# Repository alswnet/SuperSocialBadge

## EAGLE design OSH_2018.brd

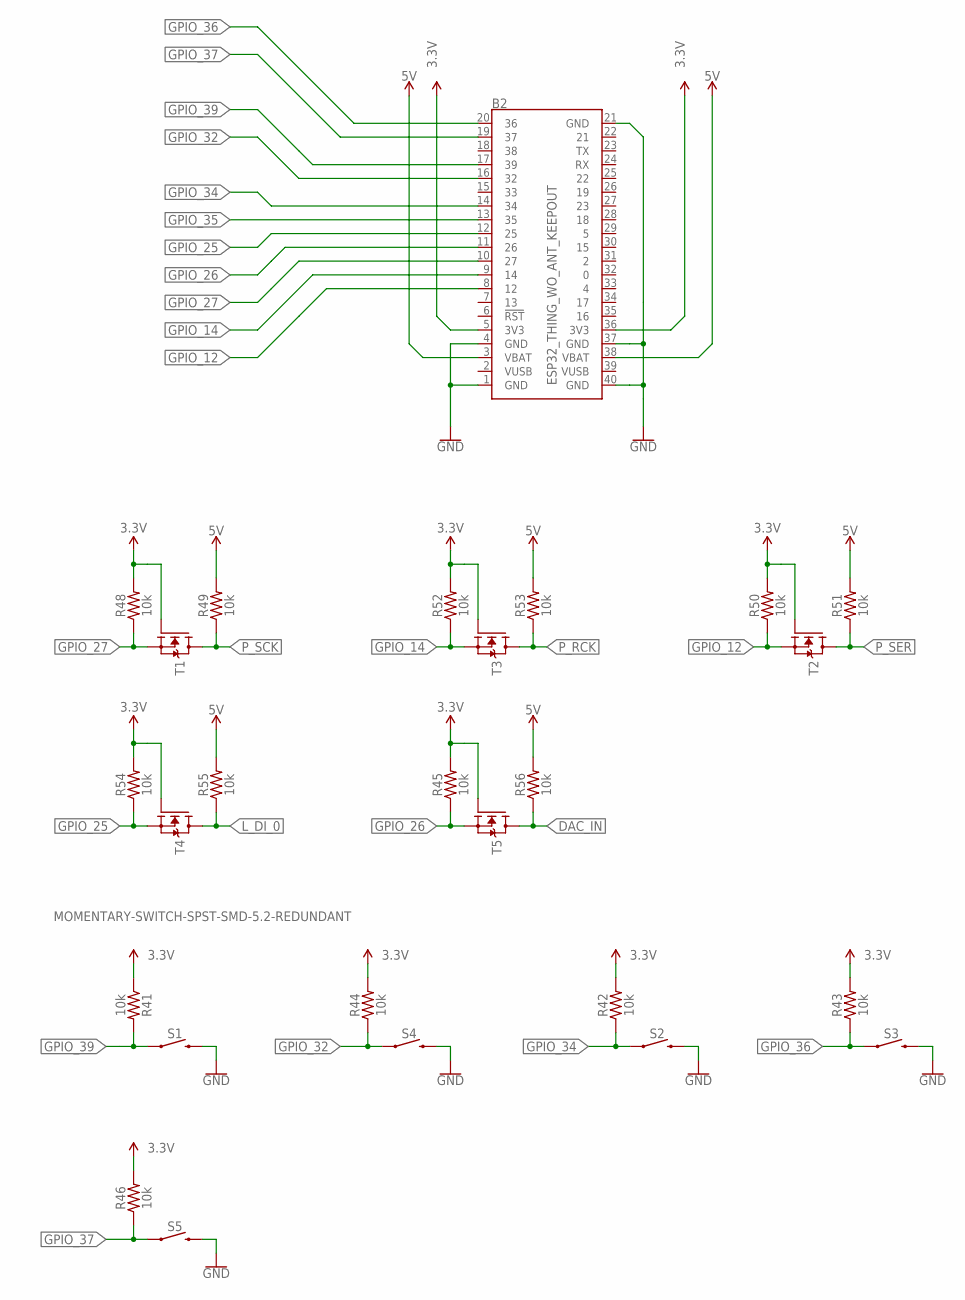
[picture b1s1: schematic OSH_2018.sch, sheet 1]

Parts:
B2: ESP32_THING_WO_ANT_KEEPOUT; ESP32_THING_NO_ANT
R41, R42, R43, R44, R45, R46, R48, R49, R50, R51, R52, R53, R54, R55, R56: 10k; 0603
S1, S2, S3, S4, S5: MOMENTARY-SWITCH-SPST-SMD-5.2-REDUNDANT; TACTILE_SWITCH_SMD_5.2MM
T1, T2, T3, T4, T5: MOSFET-N-SOT23; SOT23

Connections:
3.3V: B2.5 (3V3), B2.36 (3V3), R41.1, R42.2, R43.2, R44.2, R45.2, R46.2, R48.2, R50.2, R52.2, R54.2, T1.1 (G), T2.1 (G), T3.1 (G), T4.1 (G), T5.1 (G)
5V: B2.3 (VBAT), B2.38 (VBAT), R49.2, R51.2, R53.2, R55.2, R56.2; also elsewhere on the board
DAC_IN: R56.1, T5.3 (D); also elsewhere on the board
GND: B2.1 (GND), B2.4 (GND), B2.21 (GND), B2.37 (GND), B2.40 (GND), S1.3 (2), S1.4 (2), S2.3 (2), S2.4 (2), S3.3 (2), S3.4 (2), S4.3 (2), S4.4 (2), S5.3 (2), S5.4 (2); also elsewhere on the board
GPIO_12: B2.8 (12), R50.1, T2.2 (S)
GPIO_14: B2.9 (14), R52.1, T3.2 (S)
GPIO_25: B2.12 (25), R54.1, T4.2 (S)
GPIO_26: B2.11 (26), R45.1, T5.2 (S)
GPIO_27: B2.10 (27), R48.1, T1.2 (S)
GPIO_32: B2.16 (32), R44.1, S4.1, S4.2 (1)
GPIO_34: B2.14 (34), R42.1, S2.1, S2.2 (1)
GPIO_35: B2.13 (35); also elsewhere on the board
GPIO_36: B2.20 (36), R43.1, S3.1, S3.2 (1)
GPIO_37: B2.19 (37), R46.1, S5.1, S5.2 (1)
GPIO_39: B2.17 (39), R41.2, S1.1, S1.2 (1)
L_DI_0: R55.1, T4.3 (D); also elsewhere on the board
P_RCK: R53.1, T3.3 (D); also elsewhere on the board
P_SCK: R49.1, T1.3 (D); also elsewhere on the board
P_SER: R51.1, T2.3 (D); also elsewhere on the board

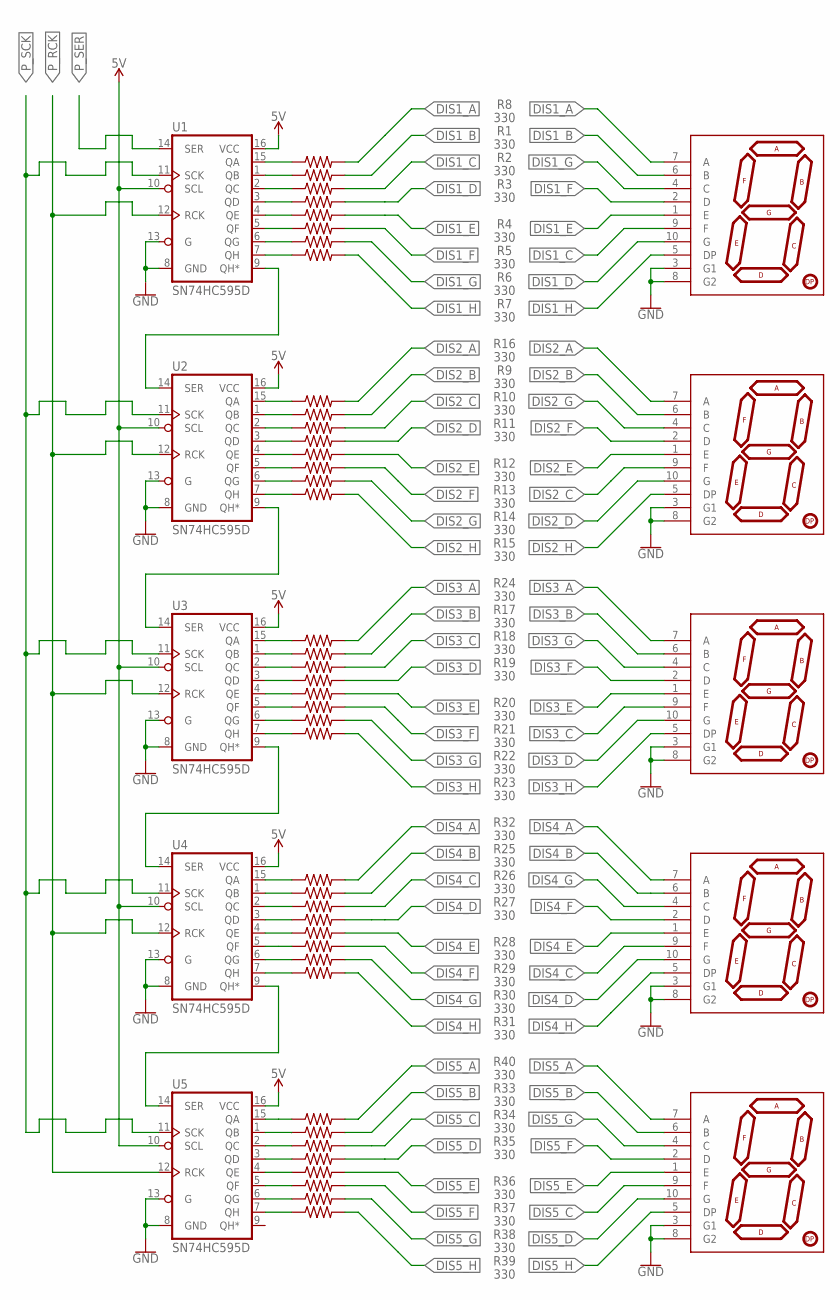
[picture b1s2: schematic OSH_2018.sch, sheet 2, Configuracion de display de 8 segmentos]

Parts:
DISPLAY_1, DISPLAY_2, DISPLAY_3, DISPLAY_4, DISPLAY_5: YSD-160AB3C-8; 7-SEGMENT-1"PTH
R1, R2, R3, R4, R5, R6, R7, R8, R9, R10, R11, R12, R13, R14, R15, R16, R17, R18, R19, R20, R21, R22, R23, R24, R25, R26, R27, R28, R29, R30, R31, R32, R33, R34, R35, R36, R37, R38, R39, R40: 330; 0603
U1, U2, U3, U4, U5: SN74HC595D; SO16

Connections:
5V: U1.10 (SCL), U1.16 (VCC), U2.10 (SCL), U2.16 (VCC), U3.10 (SCL), U3.16 (VCC), U4.10 (SCL), U4.16 (VCC), U5.10 (SCL), U5.16 (VCC); also elsewhere on the board
DIS1_A: DISPLAY_1.7 (A), R8.2
DIS1_B: DISPLAY_1.6 (B), R1.2
DIS1_C: DISPLAY_1.9 (F), R2.2
DIS1_D: DISPLAY_1.10 (G), R3.2
DIS1_E: DISPLAY_1.1 (E), R4.2
DIS1_F: DISPLAY_1.2 (D), R5.2
DIS1_G: DISPLAY_1.4 (C), R6.2
DIS1_H: DISPLAY_1.5 (DP), R7.2
DIS2_A: DISPLAY_2.7 (A), R9.2
DIS2_B: DISPLAY_2.6 (B), R10.2
DIS2_C: DISPLAY_2.9 (F), R11.2
DIS2_D: DISPLAY_2.10 (G), R12.2
DIS2_E: DISPLAY_2.1 (E), R13.2
DIS2_F: DISPLAY_2.2 (D), R14.2
DIS2_G: DISPLAY_2.4 (C), R15.2
DIS2_H: DISPLAY_2.5 (DP), R16.2
DIS3_A: DISPLAY_3.7 (A), R17.2
DIS3_B: DISPLAY_3.6 (B), R18.2
DIS3_C: DISPLAY_3.9 (F), R19.2
DIS3_D: DISPLAY_3.10 (G), R20.2
DIS3_E: DISPLAY_3.1 (E), R21.2
DIS3_F: DISPLAY_3.2 (D), R22.2
DIS3_G: DISPLAY_3.4 (C), R23.2
DIS3_H: DISPLAY_3.5 (DP), R24.2
DIS4_A: DISPLAY_4.7 (A), R25.2
DIS4_B: DISPLAY_4.6 (B), R26.2
DIS4_C: DISPLAY_4.9 (F), R27.2
DIS4_D: DISPLAY_4.10 (G), R28.2
DIS4_E: DISPLAY_4.1 (E), R29.2
DIS4_F: DISPLAY_4.2 (D), R30.2
DIS4_G: DISPLAY_4.4 (C), R31.2
DIS4_H: DISPLAY_4.5 (DP), R32.2
DIS5_A: DISPLAY_5.7 (A), R33.2
DIS5_B: DISPLAY_5.6 (B), R34.2
DIS5_C: DISPLAY_5.9 (F), R35.2
DIS5_D: DISPLAY_5.10 (G), R36.2
DIS5_E: DISPLAY_5.1 (E), R37.2
DIS5_F: DISPLAY_5.2 (D), R38.2
DIS5_G: DISPLAY_5.4 (C), R39.2
DIS5_H: DISPLAY_5.5 (DP), R40.2
GND: DISPLAY_1.3 (G1), DISPLAY_1.8 (G2), DISPLAY_2.3 (G1), DISPLAY_2.8 (G2), DISPLAY_3.3 (G1), DISPLAY_3.8 (G2), DISPLAY_4.3 (G1), DISPLAY_4.8 (G2), DISPLAY_5.3 (G1), DISPLAY_5.8 (G2), U1.8 (GND), U1.13 (G), U2.8 (GND), U2.13 (G), U3.8 (GND), U3.13 (G), U4.8 (GND), U4.13 (G), U5.8 (GND), U5.13 (G); also elsewhere on the board
unnamed: R8.1, U1.15 (QA)
unnamed: R1.1, U1.1 (QB)
unnamed: R2.1, U1.2 (QC)
unnamed: R3.1, U1.3 (QD)
unnamed: R4.1, U1.4 (QE)
unnamed: R5.1, U1.5 (QF)
unnamed: R6.1, U1.6 (QG)
unnamed: R7.1, U1.7 (QH)
unnamed: R9.1, U2.15 (QA)
unnamed: R10.1, U2.1 (QB)
unnamed: R11.1, U2.2 (QC)
unnamed: R12.1, U2.3 (QD)
unnamed: R13.1, U2.4 (QE)
unnamed: R14.1, U2.5 (QF)
unnamed: R15.1, U2.6 (QG)
unnamed: R16.1, U2.7 (QH)
unnamed: R17.1, U3.15 (QA)
unnamed: R18.1, U3.1 (QB)
unnamed: R19.1, U3.2 (QC)
unnamed: R20.1, U3.3 (QD)
unnamed: R21.1, U3.4 (QE)
unnamed: R22.1, U3.5 (QF)
unnamed: R23.1, U3.6 (QG)
unnamed: R24.1, U3.7 (QH)
unnamed: R25.1, U4.15 (QA)
unnamed: R26.1, U4.1 (QB)
unnamed: R27.1, U4.2 (QC)
unnamed: R28.1, U4.3 (QD)
unnamed: R29.1, U4.4 (QE)
unnamed: R30.1, U4.5 (QF)
unnamed: R31.1, U4.6 (QG)
unnamed: R32.1, U4.7 (QH)
unnamed: R33.1, U5.15 (QA)
unnamed: R34.1, U5.1 (QB)
unnamed: R35.1, U5.2 (QC)
unnamed: R36.1, U5.3 (QD)
unnamed: R37.1, U5.4 (QE)
unnamed: R38.1, U5.5 (QF)
unnamed: R39.1, U5.6 (QG)
unnamed: R40.1, U5.7 (QH)
unnamed: U1.9 (QH*), U2.14 (SER)
unnamed: U2.9 (QH*), U3.14 (SER)
unnamed: U3.9 (QH*), U4.14 (SER)
unnamed: U4.9 (QH*), U5.14 (SER)
P_RCK: U1.12 (RCK), U2.12 (RCK), U3.12 (RCK), U4.12 (RCK), U5.12 (RCK); also elsewhere on the board
P_SCK: U1.11 (SCK), U2.11 (SCK), U3.11 (SCK), U4.11 (SCK), U5.11 (SCK); also elsewhere on the board
P_SER: U1.14 (SER); also elsewhere on the board

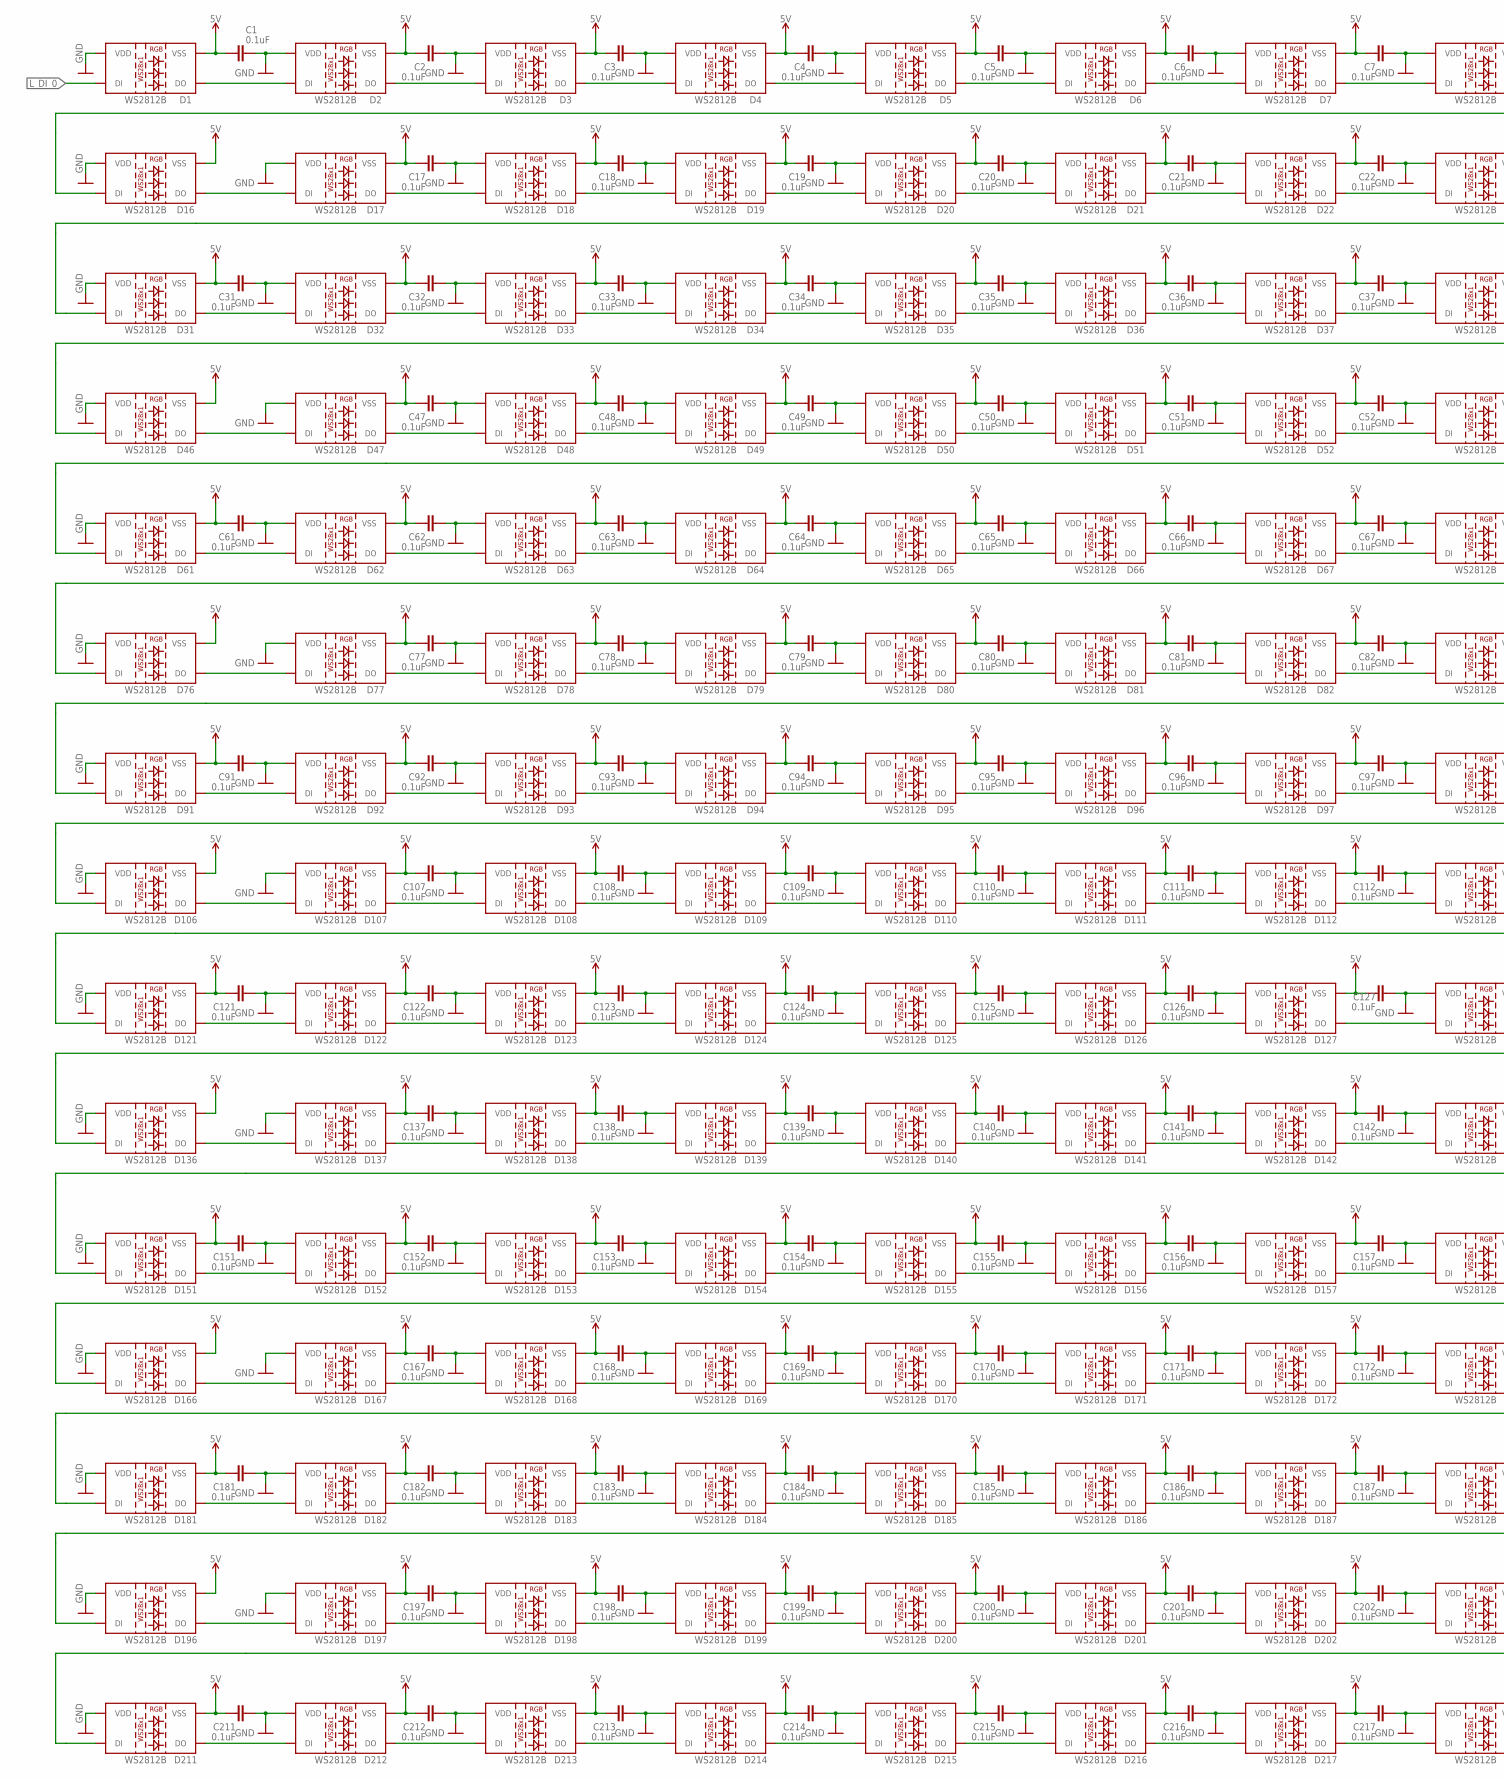
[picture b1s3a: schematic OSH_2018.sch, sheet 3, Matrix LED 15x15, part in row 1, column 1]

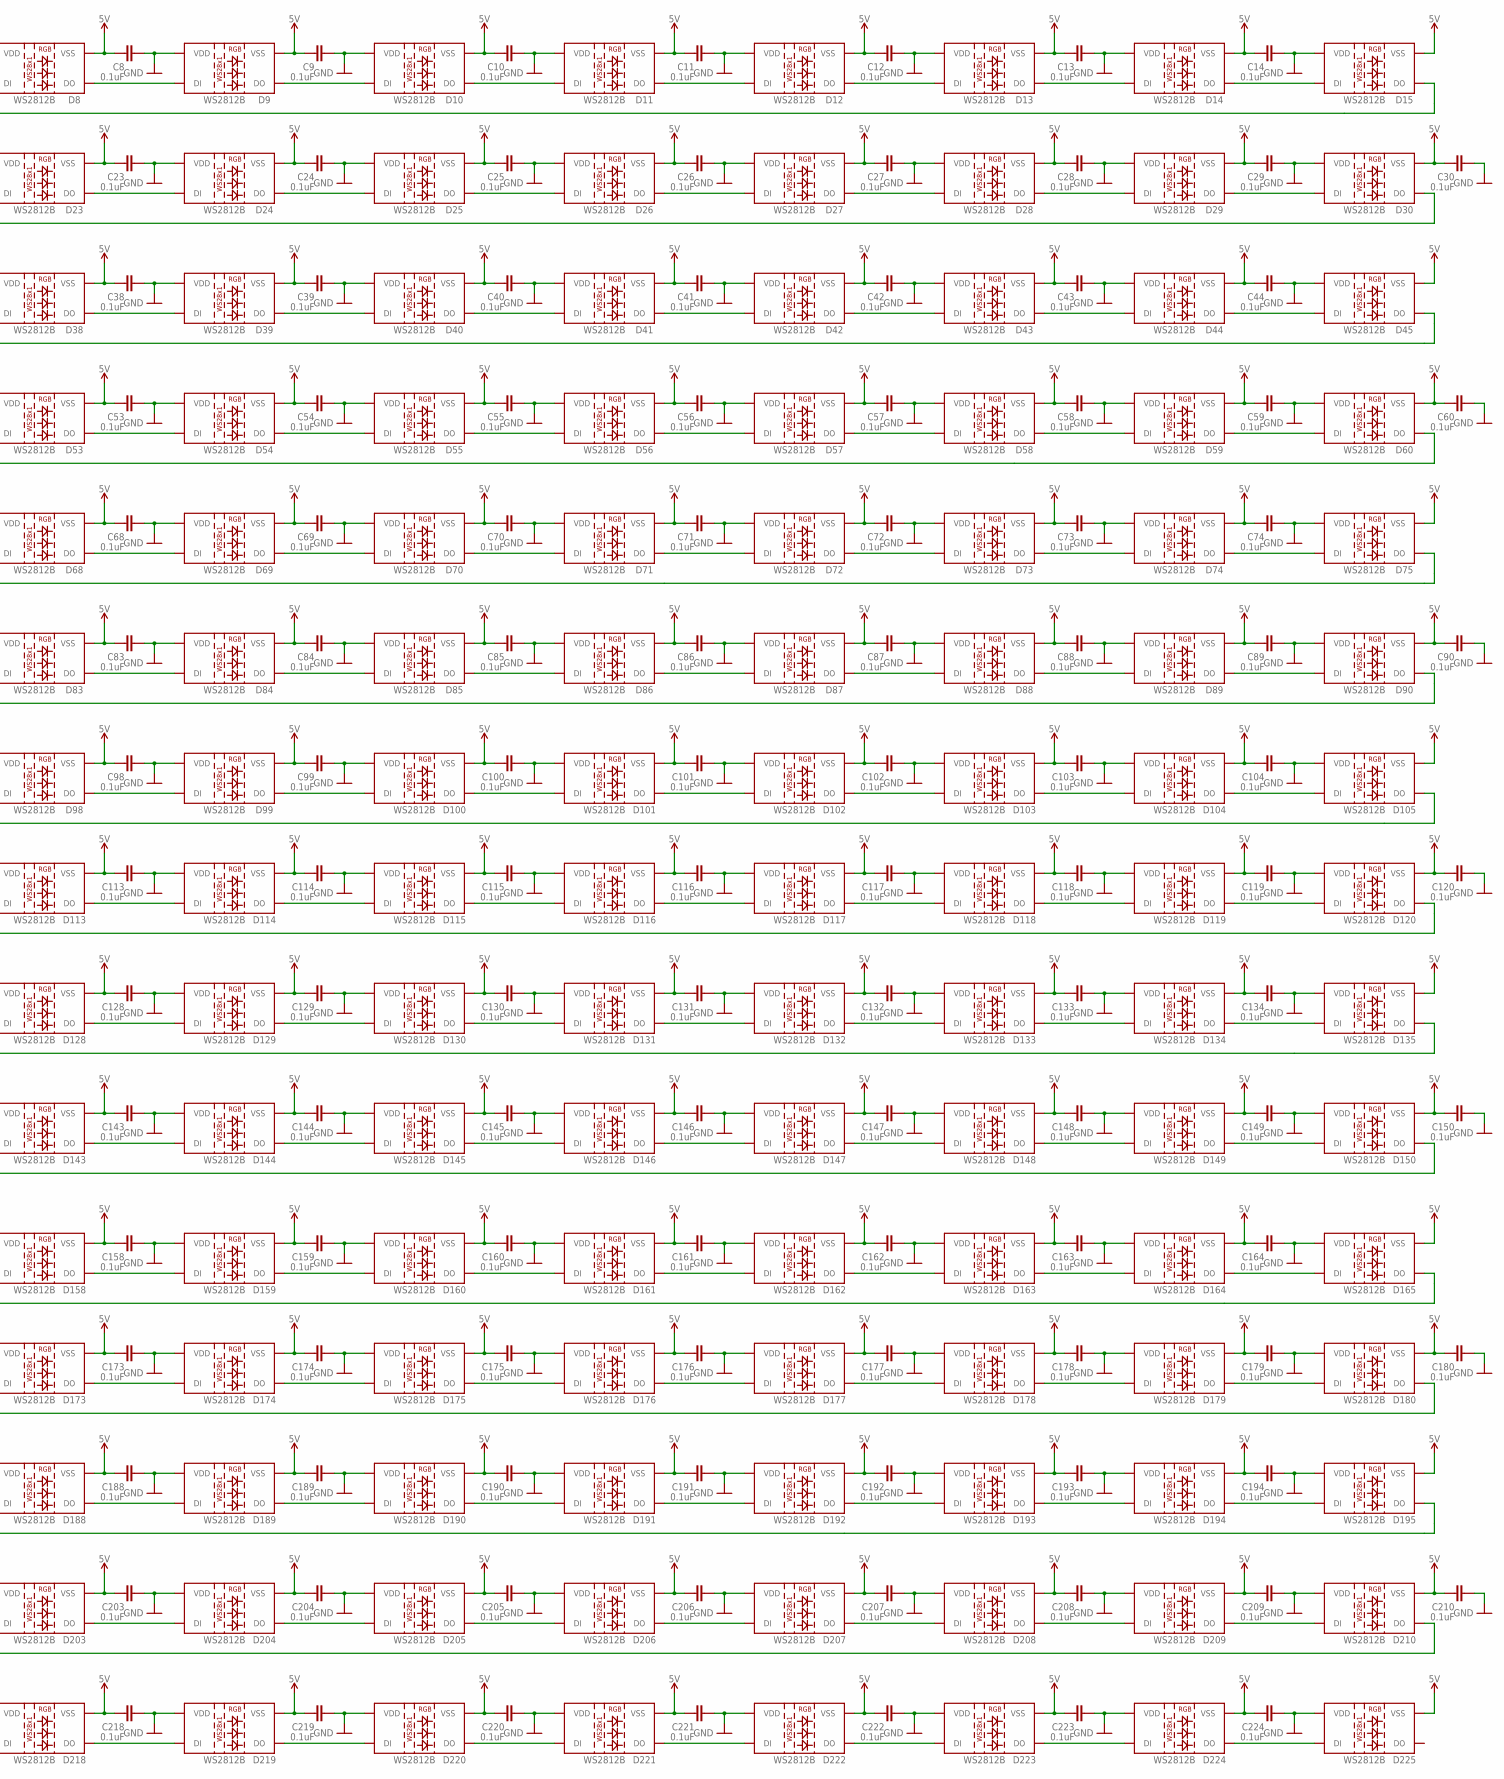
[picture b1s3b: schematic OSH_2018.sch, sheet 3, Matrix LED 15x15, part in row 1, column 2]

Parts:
C1, C2, C3, C4, C5, C6, C7, C8, C9, C10, C11, C12, C13, C14, C17, C18, C19, C20, C21, C22, C23, C24, C25, C26, C27, C28, C29, C30, C31, C32, C33, C34, C35, C36, C37, C38, C39, C40, C41, C42, C43, C44, C47, C48, C49, C50, C51, C52, C53, C54, C55, C56, C57, C58, C59, C60, C61, C62, C63, C64, C65, C66, C67, C68, C69, C70, C71, C72, C73, C74, C77, C78, C79, C80, C81, C82, C83, C84, C85, C86, C87, C88, C89, C90, C91, C92, C93, C94, C95, C96, C97, C98, C99, C100, C101, C102, C103, C104, C107, C108, C109, C110, C111, C112, C113, C114, C115, C116, C117, C118, C119, C120, C121, C122, C123, C124, C125, C126, C127, C128, C129, C130, C131, C132, C133, C134, C137, C138, C139, C140, C141, C142, C143, C144, C145, C146, C147, C148, C149, C150, C151, C152, C153, C154, C155, C156, C157, C158, C159, C160, C161, C162, C163, C164, C167, C168, C169, C170, C171, C172, C173, C174, C175, C176, C177, C178, C179, C180, C181, C182, C183, C184, C185, C186, C187, C188, C189, C190, C191, C192, C193, C194, C197, C198, C199, C200, C201, C202, C203, C204, C205, C206, C207, C208, C209, C210, C211, C212, C213, C214, C215, C216, C217, C218, C219, C220, C221, C222, C223, C224: 0.1uF; 0603
D1, D2, D3, D4, D5, D6, D7, D8, D9, D10, D11, D12, D13, D14, D15, D16, D17, D18, D19, D20, D21, D22, D23, D24, D25, D26, D27, D28, D29, D30, D31, D32, D33, D34, D35, D36, D37, D38, D39, D40, D41, D42, D43, D44, D45, D46, D47, D48, D49, D50, D51, D52, D53, D54, D55, D56, D57, D58, D59, D60, D61, D62, D63, D64, D65, D66, D67, D68, D69, D70, D71, D72, D73, D74, D75, D76, D77, D78, D79, D80, D81, D82, D83, D84, D85, D86, D87, D88, D89, D90, D91, D92, D93, D94, D95, D96, D97, D98, D99, D100, D101, D102, D103, D104, D105, D106, D107, D108, D109, D110, D111, D112, D113, D114, D115, D116, D117, D118, D119, D120, D121, D122, D123, D124, D125, D126, D127, D128, D129, D130, D131, D132, D133, D134, D135, D136, D137, D138, D139, D140, D141, D142, D143, D144, D145, D146, D147, D148, D149, D150, D151, D152, D153, D154, D155, D156, D157, D158, D159, D160, D161, D162, D163, D164, D165, D166, D167, D168, D169, D170, D171, D172, D173, D174, D175, D176, D177, D178, D179, D180, D181, D182, D183, D184, D185, D186, D187, D188, D189, D190, D191, D192, D193, D194, D195, D196, D197, D198, D199, D200, D201, D202, D203, D204, D205, D206, D207, D208, D209, D210, D211, D212, D213, D214, D215, D216, D217, D218, D219, D220, D221, D222, D223, D224, D225: WS2812B

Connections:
5V: C1.1, C2.1, C3.1, C4.1, C5.1, C6.1, C7.1, C8.1, C9.1, C10.1, C11.1, C12.1, C13.1, C14.1, C17.1, C18.1, C19.1, C20.1, C21.1, C22.1, C23.1, C24.1, C25.1, C26.1, C27.1, C28.1, C29.1, C30.1, C31.1, C32.1, C33.1, C34.1, C35.1, C36.1, C37.1, C38.1, C39.1, C40.1, C41.1, C42.1, C43.1, C44.1, C47.1, C48.1, C49.1, C50.1, C51.1, C52.1, C53.1, C54.1, C55.1, C56.1, C57.1, C58.1, C59.1, C60.1, C61.1, C62.1, C63.1, C64.1, C65.1, C66.1, C67.1, C68.1, C69.1, C70.1, C71.1, C72.1, C73.1, C74.1, C77.1, C78.1, C79.1, C80.1, C81.1, C82.1, C83.1, C84.1, C85.1, C86.1, C87.1, C88.1, C89.1, C90.1, C91.1, C92.1, C93.1, C94.1, C95.1, C96.1, C97.1, C98.1, C99.1, C100.1, C101.1, C102.1, C103.1, C104.1, C107.1, C108.1, C109.1, C110.1, C111.1, C112.1, C113.1, C114.1, C115.1, C116.1, C117.1, C118.1, C119.1, C120.1, C121.1, C122.1, C123.1, C124.1, C125.1, C126.1, C127.1, C128.1, C129.1, C130.1, C131.1, C132.1, C133.1, C134.1, C137.1, C138.1, C139.1, C140.1, C141.1, C142.1, C143.1, C144.1, C145.1, C146.1, C147.1, C148.1, C149.1, C150.1, C151.1, C152.1, C153.1, C154.1, C155.1, C156.1, C157.1, C158.1, C159.1, C160.1, C161.1, C162.1, C163.1, C164.1, C167.1, C168.1, C169.1, C170.1, C171.1, C172.1, C173.1, C174.1, C175.1, C176.1, C177.1, C178.1, C179.1, C180.1, C181.1, C182.1, C183.1, C184.1, C185.1, C186.1, C187.1, C188.1, C189.1, C190.1, C191.1, C192.1, C193.1, C194.1, C197.1, C198.1, C199.1, C200.1, C201.1, C202.1, C203.1, C204.1, C205.1, C206.1, C207.1, C208.1, C209.1, C210.1, C211.1, C212.1, C213.1, C214.1, C215.1, C216.1, C217.1, C218.1, C219.1, C220.1, C221.1, C222.1, C223.1, C224.1, D1.3 (VSS), D2.3 (VSS), D3.3 (VSS), D4.3 (VSS), D5.3 (VSS), D6.3 (VSS), D7.3 (VSS), D8.3 (VSS), D9.3 (VSS), D10.3 (VSS), D11.3 (VSS), D12.3 (VSS), D13.3 (VSS), D14.3 (VSS), D15.3 (VSS), D16.3 (VSS), D17.3 (VSS), D18.3 (VSS), D19.3 (VSS), D20.3 (VSS), D21.3 (VSS), D22.3 (VSS), D23.3 (VSS), D24.3 (VSS), D25.3 (VSS), D26.3 (VSS), D27.3 (VSS), D28.3 (VSS), D29.3 (VSS), D30.3 (VSS), D31.3 (VSS), D32.3 (VSS), D33.3 (VSS), D34.3 (VSS), D35.3 (VSS), D36.3 (VSS), D37.3 (VSS), D38.3 (VSS), D39.3 (VSS), D40.3 (VSS), D41.3 (VSS), D42.3 (VSS), D43.3 (VSS), D44.3 (VSS), D45.3 (VSS), D46.3 (VSS), D47.3 (VSS), D48.3 (VSS), D49.3 (VSS), D50.3 (VSS), D51.3 (VSS), D52.3 (VSS), D53.3 (VSS), D54.3 (VSS), D55.3 (VSS), D56.3 (VSS), D57.3 (VSS), D58.3 (VSS), D59.3 (VSS), D60.3 (VSS), D61.3 (VSS), D62.3 (VSS), D63.3 (VSS), D64.3 (VSS), D65.3 (VSS), D66.3 (VSS), D67.3 (VSS), D68.3 (VSS), D69.3 (VSS), D70.3 (VSS), D71.3 (VSS), D72.3 (VSS), D73.3 (VSS), D74.3 (VSS), D75.3 (VSS), D76.3 (VSS), D77.3 (VSS), D78.3 (VSS), D79.3 (VSS), D80.3 (VSS), D81.3 (VSS), D82.3 (VSS), D83.3 (VSS), D84.3 (VSS), D85.3 (VSS), D86.3 (VSS), D87.3 (VSS), D88.3 (VSS), D89.3 (VSS), D90.3 (VSS), D91.3 (VSS), D92.3 (VSS), D93.3 (VSS), D94.3 (VSS), D95.3 (VSS), D96.3 (VSS), D97.3 (VSS), D98.3 (VSS), D99.3 (VSS), D100.3 (VSS), D101.3 (VSS), D102.3 (VSS), D103.3 (VSS), D104.3 (VSS), D105.3 (VSS), D106.3 (VSS), D107.3 (VSS), D108.3 (VSS), D109.3 (VSS), D110.3 (VSS), D111.3 (VSS), D112.3 (VSS), D113.3 (VSS), D114.3 (VSS), D115.3 (VSS), D116.3 (VSS), D117.3 (VSS), D118.3 (VSS), D119.3 (VSS), D120.3 (VSS), D121.3 (VSS), D122.3 (VSS), D123.3 (VSS), D124.3 (VSS), D125.3 (VSS), D126.3 (VSS), D127.3 (VSS), D128.3 (VSS), D129.3 (VSS), D130.3 (VSS), D131.3 (VSS), D132.3 (VSS), D133.3 (VSS), D134.3 (VSS), D135.3 (VSS), D136.3 (VSS), D137.3 (VSS), D138.3 (VSS), D139.3 (VSS), D140.3 (VSS), D141.3 (VSS), D142.3 (VSS), D143.3 (VSS), D144.3 (VSS), D145.3 (VSS), D146.3 (VSS), D147.3 (VSS), D148.3 (VSS), D149.3 (VSS), D150.3 (VSS), D151.3 (VSS), D152.3 (VSS)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; also elsewhere on the board
GND: C1.2, C2.2, C3.2, C4.2, C5.2, C6.2, C7.2, C8.2, C9.2, C10.2, C11.2, C12.2, C13.2, C14.2, C17.2, C18.2, C19.2, C20.2, C21.2, C22.2, C23.2, C24.2, C25.2, C26.2, C27.2, C28.2, C29.2, C30.2, C31.2, C32.2, C33.2, C34.2, C35.2, C36.2, C37.2, C38.2, C39.2, C40.2, C41.2, C42.2, C43.2, C44.2, C47.2, C48.2, C49.2, C50.2, C51.2, C52.2, C53.2, C54.2, C55.2, C56.2, C57.2, C58.2, C59.2, C60.2, C61.2, C62.2, C63.2, C64.2, C65.2, C66.2, C67.2, C68.2, C69.2, C70.2, C71.2, C72.2, C73.2, C74.2, C77.2, C78.2, C79.2, C80.2, C81.2, C82.2, C83.2, C84.2, C85.2, C86.2, C87.2, C88.2, C89.2, C90.2, C91.2, C92.2, C93.2, C94.2, C95.2, C96.2, C97.2, C98.2, C99.2, C100.2, C101.2, C102.2, C103.2, C104.2, C107.2, C108.2, C109.2, C110.2, C111.2, C112.2, C113.2, C114.2, C115.2, C116.2, C117.2, C118.2, C119.2, C120.2, C121.2, C122.2, C123.2, C124.2, C125.2, C126.2, C127.2, C128.2, C129.2, C130.2, C131.2, C132.2, C133.2, C134.2, C137.2, C138.2, C139.2, C140.2, C141.2, C142.2, C143.2, C144.2, C145.2, C146.2, C147.2, C148.2, C149.2, C150.2, C151.2, C152.2, C153.2, C154.2, C155.2, C156.2, C157.2, C158.2, C159.2, C160.2, C161.2, C162.2, C163.2, C164.2, C167.2, C168.2, C169.2, C170.2, C171.2, C172.2, C173.2, C174.2, C175.2, C176.2, C177.2, C178.2, C179.2, C180.2, C181.2, C182.2, C183.2, C184.2, C185.2, C186.2, C187.2, C188.2, C189.2, C190.2, C191.2, C192.2, C193.2, C194.2, C197.2, C198.2, C199.2, C200.2, C201.2, C202.2, C203.2, C204.2, C205.2, C206.2, C207.2, C208.2, C209.2, C210.2, C211.2, C212.2, C213.2, C214.2, C215.2, C216.2, C217.2, C218.2, C219.2, C220.2, C221.2, C222.2, C223.2, C224.2, D1.1 (VDD), D2.1 (VDD), D3.1 (VDD), D4.1 (VDD), D5.1 (VDD), D6.1 (VDD), D7.1 (VDD), D8.1 (VDD), D9.1 (VDD), D10.1 (VDD), D11.1 (VDD), D12.1 (VDD), D13.1 (VDD), D14.1 (VDD), D15.1 (VDD), D16.1 (VDD), D17.1 (VDD), D18.1 (VDD), D19.1 (VDD), D20.1 (VDD), D21.1 (VDD), D22.1 (VDD), D23.1 (VDD), D24.1 (VDD), D25.1 (VDD), D26.1 (VDD), D27.1 (VDD), D28.1 (VDD), D29.1 (VDD), D30.1 (VDD), D31.1 (VDD), D32.1 (VDD), D33.1 (VDD), D34.1 (VDD), D35.1 (VDD), D36.1 (VDD), D37.1 (VDD), D38.1 (VDD), D39.1 (VDD), D40.1 (VDD), D41.1 (VDD), D42.1 (VDD), D43.1 (VDD), D44.1 (VDD), D45.1 (VDD), D46.1 (VDD), D47.1 (VDD), D48.1 (VDD), D49.1 (VDD), D50.1 (VDD), D51.1 (VDD), D52.1 (VDD), D53.1 (VDD), D54.1 (VDD), D55.1 (VDD), D56.1 (VDD), D57.1 (VDD), D58.1 (VDD), D59.1 (VDD), D60.1 (VDD), D61.1 (VDD), D62.1 (VDD), D63.1 (VDD), D64.1 (VDD), D65.1 (VDD), D66.1 (VDD), D67.1 (VDD), D68.1 (VDD), D69.1 (VDD), D70.1 (VDD), D71.1 (VDD), D72.1 (VDD), D73.1 (VDD), D74.1 (VDD), D75.1 (VDD), D76.1 (VDD), D77.1 (VDD), D78.1 (VDD), D79.1 (VDD), D80.1 (VDD), D81.1 (VDD), D82.1 (VDD), D83.1 (VDD), D84.1 (VDD), D85.1 (VDD), D86.1 (VDD), D87.1 (VDD), D88.1 (VDD), D89.1 (VDD), D90.1 (VDD), D91.1 (VDD), D92.1 (VDD), D93.1 (VDD), D94.1 (VDD), D95.1 (VDD), D96.1 (VDD), D97.1 (VDD), D98.1 (VDD), D99.1 (VDD), D100.1 (VDD), D101.1 (VDD), D102.1 (VDD), D103.1 (VDD), D104.1 (VDD), D105.1 (VDD), D106.1 (VDD), D107.1 (VDD), D108.1 (VDD), D109.1 (VDD), D110.1 (VDD), D111.1 (VDD), D112.1 (VDD), D113.1 (VDD), D114.1 (VDD), D115.1 (VDD), D116.1 (VDD), D117.1 (VDD), D118.1 (VDD), D119.1 (VDD), D120.1 (VDD), D121.1 (VDD), D122.1 (VDD), D123.1 (VDD), D124.1 (VDD), D125.1 (VDD), D126.1 (VDD), D127.1 (VDD), D128.1 (VDD), D129.1 (VDD), D130.1 (VDD), D131.1 (VDD), D132.1 (VDD), D133.1 (VDD), D134.1 (VDD), D135.1 (VDD), D136.1 (VDD), D137.1 (VDD), D138.1 (VDD), D139.1 (VDD), D140.1 (VDD), D141.1 (VDD), D142.1 (VDD), D143.1 (VDD), D144.1 (VDD), D145.1 (VDD), D146.1 (VDD), D147.1 (VDD), D148.1 (VDD), D149.1 (VDD), D150.1 (VDD), D151.1 (VDD), D152.1 (VDD)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; also elsewhere on the board
L_DI_0: D1.4 (DI); also elsewhere on the board
unnamed: D1.2 (DO), D2.4 (DI)
unnamed: D2.2 (DO), D3.4 (DI)
unnamed: D3.2 (DO), D4.4 (DI)
unnamed: D4.2 (DO), D5.4 (DI)
unnamed: D5.2 (DO), D6.4 (DI)
unnamed: D6.2 (DO), D7.4 (DI)
unnamed: D7.2 (DO), D8.4 (DI)
unnamed: D8.2 (DO), D9.4 (DI)
unnamed: D9.2 (DO), D10.4 (DI)
unnamed: D10.2 (DO), D11.4 (DI)
unnamed: D11.2 (DO), D12.4 (DI)
unnamed: D12.2 (DO), D13.4 (DI)
unnamed: D13.2 (DO), D14.4 (DI)
unnamed: D14.2 (DO), D15.4 (DI)
unnamed: D15.2 (DO), D16.4 (DI)
unnamed: D16.2 (DO), D17.4 (DI)
unnamed: D17.2 (DO), D18.4 (DI)
unnamed: D18.2 (DO), D19.4 (DI)
unnamed: D19.2 (DO), D20.4 (DI)
unnamed: D20.2 (DO), D21.4 (DI)
unnamed: D21.2 (DO), D22.4 (DI)
unnamed: D22.2 (DO), D23.4 (DI)
unnamed: D23.2 (DO), D24.4 (DI)
unnamed: D24.2 (DO), D25.4 (DI)
unnamed: D25.2 (DO), D26.4 (DI)
unnamed: D26.2 (DO), D27.4 (DI)
unnamed: D27.2 (DO), D28.4 (DI)
unnamed: D28.2 (DO), D29.4 (DI)
unnamed: D29.2 (DO), D30.4 (DI)
unnamed: D30.2 (DO), D31.4 (DI)
unnamed: D31.2 (DO), D32.4 (DI)
unnamed: D32.2 (DO), D33.4 (DI)
unnamed: D33.2 (DO), D34.4 (DI)
unnamed: D34.2 (DO), D35.4 (DI)
unnamed: D35.2 (DO), D36.4 (DI)
unnamed: D36.2 (DO), D37.4 (DI)
unnamed: D37.2 (DO), D38.4 (DI)
unnamed: D38.2 (DO), D39.4 (DI)
unnamed: D39.2 (DO), D40.4 (DI)
unnamed: D40.2 (DO), D41.4 (DI)
unnamed: D41.2 (DO), D42.4 (DI)
unnamed: D42.2 (DO), D43.4 (DI)
unnamed: D43.2 (DO), D44.4 (DI)
unnamed: D44.2 (DO), D45.4 (DI)
unnamed: D45.2 (DO), D46.4 (DI)
unnamed: D46.2 (DO), D47.4 (DI)
unnamed: D47.2 (DO), D48.4 (DI)
unnamed: D48.2 (DO), D49.4 (DI)
unnamed: D49.2 (DO), D50.4 (DI)
unnamed: D50.2 (DO), D51.4 (DI)
unnamed: D51.2 (DO), D52.4 (DI)
unnamed: D52.2 (DO), D53.4 (DI)
unnamed: D53.2 (DO), D54.4 (DI)
unnamed: D54.2 (DO), D55.4 (DI)
unnamed: D55.2 (DO), D56.4 (DI)
unnamed: D56.2 (DO), D57.4 (DI)
unnamed: D57.2 (DO), D58.4 (DI)
unnamed: D58.2 (DO), D59.4 (DI)
unnamed: D59.2 (DO), D60.4 (DI)
unnamed: D60.2 (DO), D61.4 (DI)
unnamed: D61.2 (DO), D62.4 (DI)
unnamed: D62.2 (DO), D63.4 (DI)
unnamed: D63.2 (DO), D64.4 (DI)
unnamed: D64.2 (DO), D65.4 (DI)
unnamed: D65.2 (DO), D66.4 (DI)
unnamed: D66.2 (DO), D67.4 (DI)
unnamed: D67.2 (DO), D68.4 (DI)
unnamed: D68.2 (DO), D69.4 (DI)
unnamed: D69.2 (DO), D70.4 (DI)
unnamed: D70.2 (DO), D71.4 (DI)
unnamed: D71.2 (DO), D72.4 (DI)
unnamed: D72.2 (DO), D73.4 (DI)
unnamed: D73.2 (DO), D74.4 (DI)
unnamed: D74.2 (DO), D75.4 (DI)
unnamed: D75.2 (DO), D76.4 (DI)
unnamed: D76.2 (DO), D77.4 (DI)
unnamed: D77.2 (DO), D78.4 (DI)
unnamed: D78.2 (DO), D79.4 (DI)
unnamed: D79.2 (DO), D80.4 (DI)
unnamed: D80.2 (DO), D81.4 (DI)
unnamed: D81.2 (DO), D82.4 (DI)
unnamed: D82.2 (DO), D83.4 (DI)
unnamed: D83.2 (DO), D84.4 (DI)
unnamed: D84.2 (DO), D85.4 (DI)
unnamed: D85.2 (DO), D86.4 (DI)
unnamed: D86.2 (DO), D87.4 (DI)
unnamed: D87.2 (DO), D88.4 (DI)
unnamed: D88.2 (DO), D89.4 (DI)
unnamed: D89.2 (DO), D90.4 (DI)
unnamed: D90.2 (DO), D91.4 (DI)
unnamed: D91.2 (DO), D92.4 (DI)
unnamed: D92.2 (DO), D93.4 (DI)
unnamed: D93.2 (DO), D94.4 (DI)
unnamed: D94.2 (DO), D95.4 (DI)
unnamed: D95.2 (DO), D96.4 (DI)
unnamed: D96.2 (DO), D97.4 (DI)
unnamed: D97.2 (DO), D98.4 (DI)
unnamed: D98.2 (DO), D99.4 (DI)
unnamed: D99.2 (DO), D100.4 (DI)
unnamed: D100.2 (DO), D101.4 (DI)
unnamed: D101.2 (DO), D102.4 (DI)
unnamed: D102.2 (DO), D103.4 (DI)
unnamed: D103.2 (DO), D104.4 (DI)
unnamed: D104.2 (DO), D105.4 (DI)
unnamed: D105.2 (DO), D106.4 (DI)
unnamed: D106.2 (DO), D107.4 (DI)
unnamed: D107.2 (DO), D108.4 (DI)
unnamed: D108.2 (DO), D109.4 (DI)
unnamed: D109.2 (DO), D110.4 (DI)
unnamed: D110.2 (DO), D111.4 (DI)
unnamed: D111.2 (DO), D112.4 (DI)
unnamed: D112.2 (DO), D113.4 (DI)
unnamed: D113.2 (DO), D114.4 (DI)
unnamed: D114.2 (DO), D115.4 (DI)
unnamed: D115.2 (DO), D116.4 (DI)
unnamed: D116.2 (DO), D117.4 (DI)
unnamed: D117.2 (DO), D118.4 (DI)
unnamed: D118.2 (DO), D119.4 (DI)
unnamed: D119.2 (DO), D120.4 (DI)
unnamed: D120.2 (DO), D121.4 (DI)
unnamed: D121.2 (DO), D122.4 (DI)
unnamed: D122.2 (DO), D123.4 (DI)
unnamed: D123.2 (DO), D124.4 (DI)
unnamed: D124.2 (DO), D125.4 (DI)
unnamed: D125.2 (DO), D126.4 (DI)
unnamed: D126.2 (DO), D127.4 (DI)
unnamed: D127.2 (DO), D128.4 (DI)
unnamed: D128.2 (DO), D129.4 (DI)
unnamed: D129.2 (DO), D130.4 (DI)
unnamed: D130.2 (DO), D131.4 (DI)
unnamed: D131.2 (DO), D132.4 (DI)
unnamed: D132.2 (DO), D133.4 (DI)
unnamed: D133.2 (DO), D134.4 (DI)
unnamed: D134.2 (DO), D135.4 (DI)
unnamed: D135.2 (DO), D136.4 (DI)
unnamed: D136.2 (DO), D137.4 (DI)
unnamed: D137.2 (DO), D138.4 (DI)
unnamed: D138.2 (DO), D139.4 (DI)
unnamed: D139.2 (DO), D140.4 (DI)
unnamed: D140.2 (DO), D141.4 (DI)
unnamed: D141.2 (DO), D142.4 (DI)
unnamed: D142.2 (DO), D143.4 (DI)
unnamed: D143.2 (DO), D144.4 (DI)
unnamed: D144.2 (DO), D145.4 (DI)
unnamed: D145.2 (DO), D146.4 (DI)
unnamed: D146.2 (DO), D147.4 (DI)
unnamed: D147.2 (DO), D148.4 (DI)
unnamed: D148.2 (DO), D149.4 (DI)
unnamed: D149.2 (DO), D150.4 (DI)
unnamed: D150.2 (DO), D151.4 (DI)
unnamed: D151.2 (DO), D152.4 (DI)
unnamed: D152.2 (DO), D153.4 (DI)
unnamed: D153.2 (DO), D154.4 (DI)
unnamed: D154.2 (DO), D155.4 (DI)
unnamed: D155.2 (DO), D156.4 (DI)
unnamed: D156.2 (DO), D157.4 (DI)
unnamed: D157.2 (DO), D158.4 (DI)
unnamed: D158.2 (DO), D159.4 (DI)
unnamed: D159.2 (DO), D160.4 (DI)
unnamed: D160.2 (DO), D161.4 (DI)
unnamed: D161.2 (DO), D162.4 (DI)
unnamed: D162.2 (DO), D163.4 (DI)
unnamed: D163.2 (DO), D164.4 (DI)
unnamed: D164.2 (DO), D165.4 (DI)
unnamed: D165.2 (DO), D166.4 (DI)
unnamed: D166.2 (DO), D167.4 (DI)
unnamed: D167.2 (DO), D168.4 (DI)
unnamed: D168.2 (DO), D169.4 (DI)
unnamed: D169.2 (DO), D170.4 (DI)
unnamed: D170.2 (DO), D171.4 (DI)
unnamed: D171.2 (DO), D172.4 (DI)
unnamed: D172.2 (DO), D173.4 (DI)
unnamed: D173.2 (DO), D174.4 (DI)
unnamed: D174.2 (DO), D175.4 (DI)
unnamed: D175.2 (DO), D176.4 (DI)
unnamed: D176.2 (DO), D177.4 (DI)
unnamed: D177.2 (DO), D178.4 (DI)
unnamed: D178.2 (DO), D179.4 (DI)
unnamed: D179.2 (DO), D180.4 (DI)
unnamed: D180.2 (DO), D181.4 (DI)
unnamed: D181.2 (DO), D182.4 (DI)
unnamed: D182.2 (DO), D183.4 (DI)
unnamed: D183.2 (DO), D184.4 (DI)
unnamed: D184.2 (DO), D185.4 (DI)
unnamed: D185.2 (DO), D186.4 (DI)
unnamed: D186.2 (DO), D187.4 (DI)
unnamed: D187.2 (DO), D188.4 (DI)
unnamed: D188.2 (DO), D189.4 (DI)
unnamed: D189.2 (DO), D190.4 (DI)
unnamed: D190.2 (DO), D191.4 (DI)
unnamed: D191.2 (DO), D192.4 (DI)
unnamed: D192.2 (DO), D193.4 (DI)
unnamed: D193.2 (DO), D194.4 (DI)
unnamed: D194.2 (DO), D195.4 (DI)
unnamed: D195.2 (DO), D196.4 (DI)
unnamed: D196.2 (DO), D197.4 (DI)
unnamed: D197.2 (DO), D198.4 (DI)
unnamed: D198.2 (DO), D199.4 (DI)
unnamed: D199.2 (DO), D200.4 (DI)
unnamed: D200.2 (DO), D201.4 (DI)
unnamed: D201.2 (DO), D202.4 (DI)
unnamed: D202.2 (DO), D203.4 (DI)
unnamed: D203.2 (DO), D204.4 (DI)
unnamed: D204.2 (DO), D205.4 (DI)
unnamed: D205.2 (DO), D206.4 (DI)
unnamed: D206.2 (DO), D207.4 (DI)
unnamed: D207.2 (DO), D208.4 (DI)
unnamed: D208.2 (DO), D209.4 (DI)
unnamed: D209.2 (DO), D210.4 (DI)
unnamed: D210.2 (DO), D211.4 (DI)
unnamed: D211.2 (DO), D212.4 (DI)
unnamed: D212.2 (DO), D213.4 (DI)
unnamed: D213.2 (DO), D214.4 (DI)
unnamed: D214.2 (DO), D215.4 (DI)
unnamed: D215.2 (DO), D216.4 (DI)
unnamed: D216.2 (DO), D217.4 (DI)
unnamed: D217.2 (DO), D218.4 (DI)
unnamed: D218.2 (DO), D219.4 (DI)
unnamed: D219.2 (DO), D220.4 (DI)
unnamed: D220.2 (DO), D221.4 (DI)
unnamed: D221.2 (DO), D222.4 (DI)
unnamed: D222.2 (DO), D223.4 (DI)
unnamed: D223.2 (DO), D224.4 (DI)
unnamed: D224.2 (DO), D225.4 (DI)

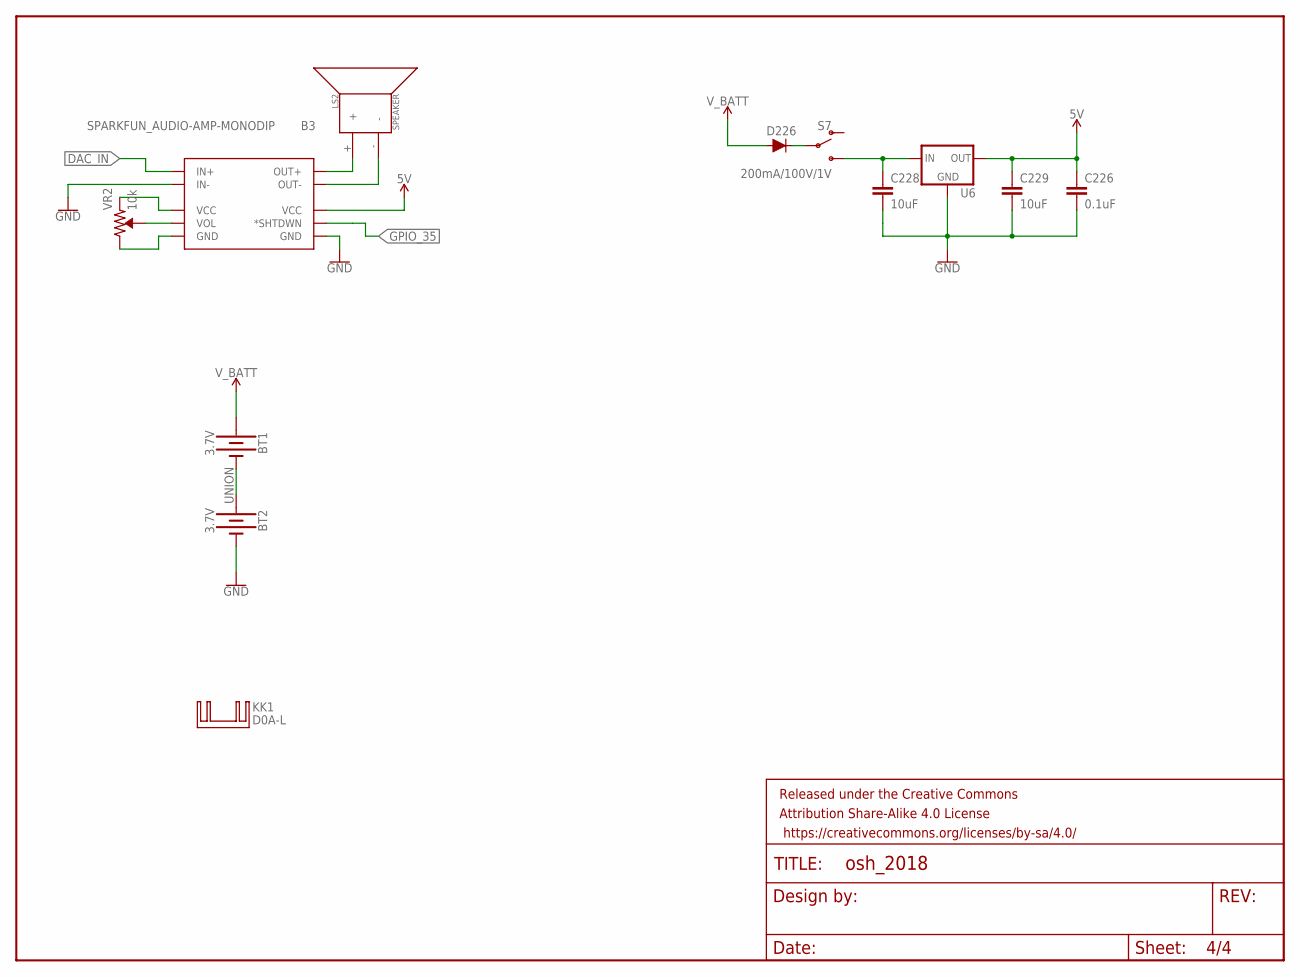
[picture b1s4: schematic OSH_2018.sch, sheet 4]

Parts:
B3: SPARKFUN_AUDIO-AMP-MONODIP; AUDIO-AMP-MONO
BT1, BT2: 3.7V; BATTERY_18650-HOLDER
C226: 0.1uF; 0603
C228, C229: 10uF; 0603
D226: 200mA/100V/1V; DIODE-1N4148
FRAME3: FRAME-LETTERNO_PACKAGE; DUMMY
KK1: D0A-L; D02A-L
LS2: SPEAKER; PCB_MOUNT_SPEAKER
S7: SWITCH-SPDT-SMD-RIGHT-ANGLE; SWITCH_SPST_SMD_A
U6: V_REG_78XX-TO-220; TO-220-ALT
VR2: 10k; TRIMPOT-PTH-3386U

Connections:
5V: B3.PWR+ (VCC), C226.1, C229.1, U6.OUT; also elsewhere on the board
DAC_IN: B3.IN+; also elsewhere on the board
GND: B3.IN-, B3.PWR- (GND), BT2.GND@1 (-), C226.2, C228.2, C229.2, U6.GND; also elsewhere on the board
GPIO_35: B3.S (*SHTDWN); also elsewhere on the board
unnamed: C228.1, S7.3 (S), U6.IN
unnamed: D226.C, S7.2
unnamed: B3.OUT-, LS2.-
unnamed: B3.OUT+, LS2.+
unnamed: B3.VOL, VR2.2 (WIPER)
unnamed: B3.VOL- (GND), VR2.3 (CW)
unnamed: B3.VOL+ (VCC), VR2.1 (CCW)
UNION: BT1.GND@1 (-), BT2.PWR@1 (+)
V_BATT: BT1.PWR@1 (+), D226.A

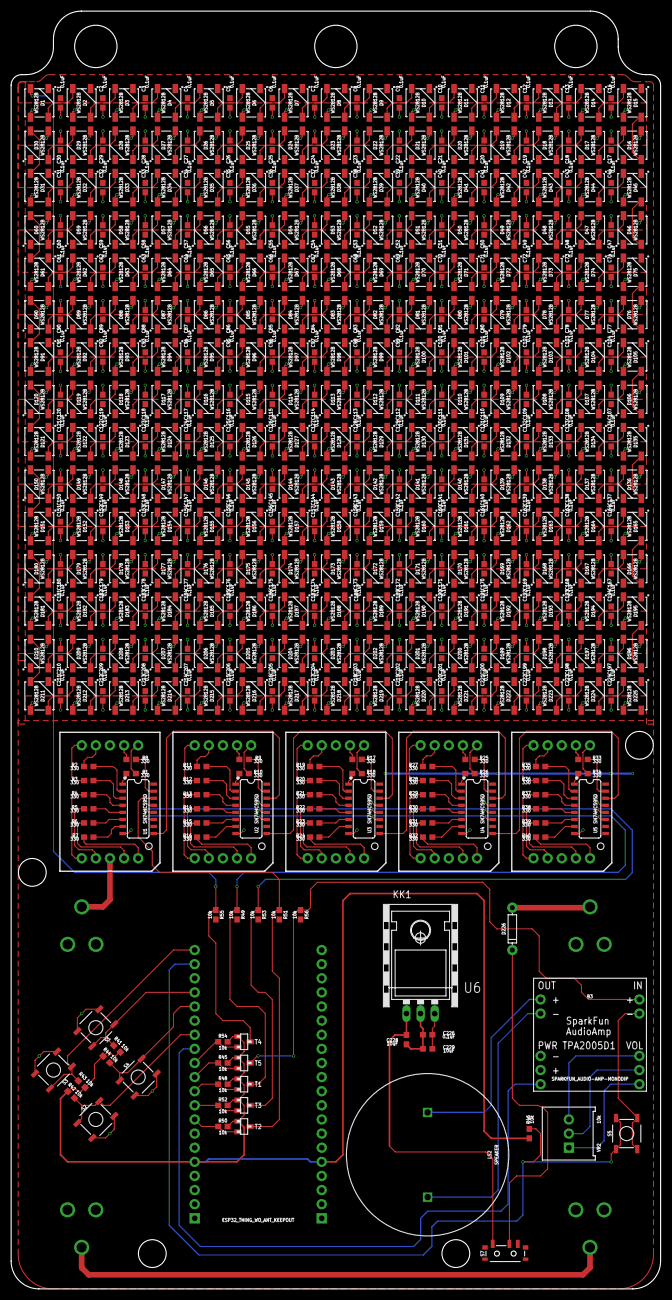
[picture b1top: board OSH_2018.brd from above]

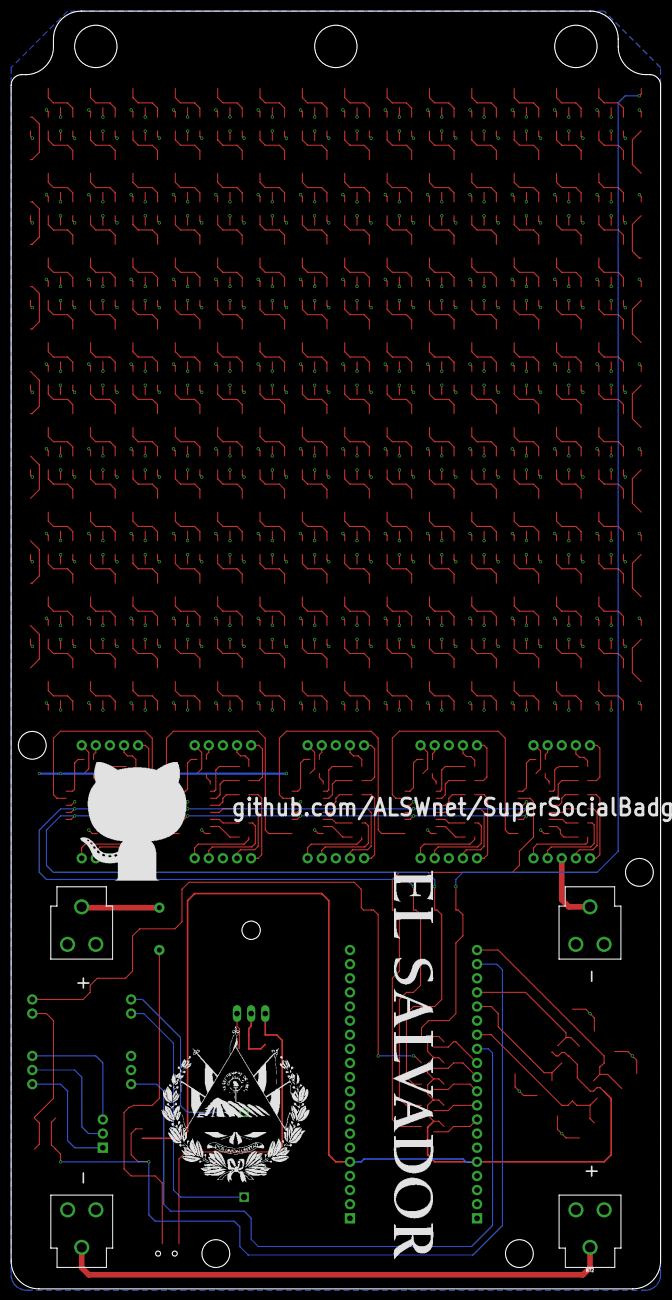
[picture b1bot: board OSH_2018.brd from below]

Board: 2 copper layers, 116.8 x 229.9 mm, 524 parts (2 on the bottom side), 336 nets.

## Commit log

2018-09-06 Agregando git ignore para archivos de eagle
2018-09-06 Placa de pantalla con neopixel y esp32
2018-09-06 Esquematico con neopixel y esp32
2018-09-10 ordenando los disenos en la carpeta hardware
2018-09-10 codigo base del SuperSocialDisplay
2018-09-12 Agregado funcionalidas a la SD
2018-09-13 app base para mandas los imagenes
2018-09-13 Mejorando sistema multi sistema y agregando modo app
2018-09-13 Agregando funciones de BT
2018-09-14 Guardas Frame en memoria
2018-09-14 Guardando imagen y mostrando en pantalla
2018-09-17 Actualizando los pines del Pantalla
2018-09-18 Sistema de Guardas en SD la posicion del GPS y un led indicador Listo
2018-09-18 App Base con colores y pantalla
2018-09-19 Agregando informacion del nombre de BT y reparando el sistema para cargarlo
2018-09-26 COdigo antes de mepezar en hakerspace boston
2018-09-26 cambiando la libreria del NeoPixel
2018-09-26 Agregando un boton
2018-10-03 Suviendo app y codigo mejorar de Android

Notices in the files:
parts and their libraries:
SparkFun-Boards: Licensing: Creative Commons ShareAlike 4.0 International - https://creativecommons.org/licenses/by-sa/4.0
SparkFun-Aesthetics: Released under the Creative Commons Attribution Share-Alike 4.0 License
SparkFun-Aesthetics: https://creativecommons.org/licenses/by-sa/4.0
